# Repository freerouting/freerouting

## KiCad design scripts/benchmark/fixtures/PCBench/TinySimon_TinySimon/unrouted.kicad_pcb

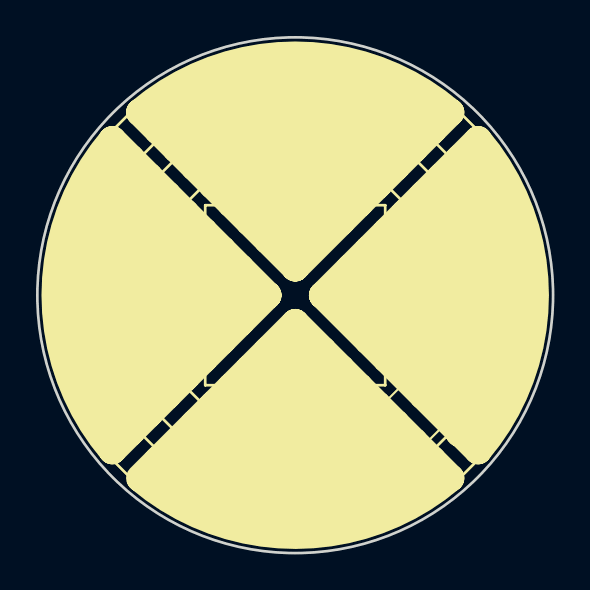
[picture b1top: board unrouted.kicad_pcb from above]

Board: 2 copper layers, 28.7 x 28.7 mm, 20 parts (0 on the bottom side), 10 nets, no tracks yet.

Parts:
B1: CR2032; BAT-HLD-001
D1: APT3216LSECK/J3-PRV; LED_1206
D2: APT3216LSYCK/J3-PRV; LED_1206
D3: APT3216LZGCK; LED_1206
D4: APT3216LVBC/D; LED_1206
P1: PIC ICSP; Pads_1x5_Pitch1.27mm
R1, R2, R3, R4: 1M; R_1206
R6, R7, R8, R9: 1K; R_1206
SW1, SW2, SW3, SW4: FSMSM; SW_SPST_FSMSM
U1: PIC10F200T; SOT-23-6
Y1: PKMCS0909E4000-R1; Murata_Piezo_SMD_9x9mm

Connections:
+BATT: B1.1, P1.2, R1.1, R2.1, R3.1, R4.1, U1.5
GND: B1.2, P1.3, SW1.2, SW2.2, SW3.2, SW4.2, U1.2
unnamed: D1.1, D2.2, R1.2, R7.1, R9.2, SW1.1
unnamed: D1.2, D2.1, D3.1, D4.2, R3.2, R6.1, SW3.1
unnamed: D3.2, D4.1, R4.2, R8.1, SW4.1, Y1.2
unnamed: P1.1, R2.2, SW2.1, U1.6
unnamed: P1.4, R6.2, U1.1
unnamed: P1.5, R7.2, U1.3
unnamed: R8.2, U1.4
unnamed: R9.1, Y1.1

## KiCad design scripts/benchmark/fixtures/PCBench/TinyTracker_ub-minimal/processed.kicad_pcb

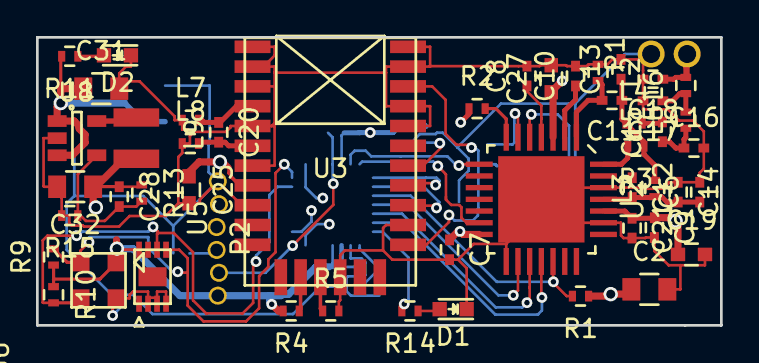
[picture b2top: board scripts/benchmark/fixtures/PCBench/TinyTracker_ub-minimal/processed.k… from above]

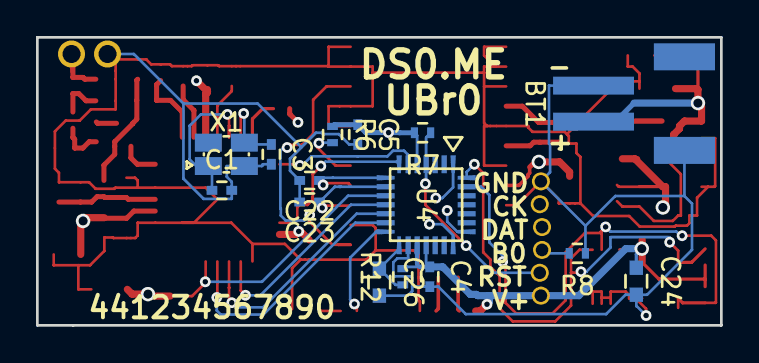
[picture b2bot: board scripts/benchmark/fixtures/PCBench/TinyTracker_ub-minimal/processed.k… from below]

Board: 4 copper layers, 38.0 x 16.0 mm, 65 parts (15 on the bottom side), 42 nets.

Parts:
BT1: LiPoly; S2B-PH-SM4-TB
C1, C3: 10p; C_0402
C2, C32: 10u; C_0805
C4, C5, C7, C8, C10: 100n; C_0402
C6: 10n; C_0402
C9, C12, C15: 47p; C_0402
C11: *2.2p; C_0402
C13: 6.8p; C_0402
C14: 100p; C_0402
C16: 15p; C_0402
C17: 12p; C_0402
C18: 4.7p; C_0402
C19: 2.2u; C_0603
C20: 18p; C_0402
C21, C22, C23: 22p; C_0402
C24, C25, C26, C27: 1u; C_0603
C28: 8.2p; C_0402
C31: 4.7u; C_0805
D1: RED; LED-0603
D2: GREEN; LED-0603
L2: *18nH; R_0402
L3: 47nH; R_0402
L4: 22n; R_0402
L5: 12n; R_0402
L6: 18n; R_0402
L7, L8: DNP; R_0402
L9: 74479787222; Neosid_Inductor_SM-NE29_SMD1008
P1: ANT; ANT_50ohm
P2: CONN_01X06; 6-1.27mm
R1, R2, R4, R5, R6, R9, R10: 10k; R_0402
R3: 0; R_0402
R7, R8, R12, R15: 100k; R_0402
R11: 2.2k; R_0402
R13: 300k; R_0402
R14: 220; R_0402
U2: SX1276; QFP_28_0.65
U3: M10478; M10748
U4: STM32F048GUx; UFQFPN28
U5: CAT24M01; UDFN8
U6: MS5637
U8: LM3671; SOT-23-5
X1: 32M; XTAL-2x2.5

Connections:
+1V8: C2.1, C4.1, C5.1, C7.1, C9.1, C19.1, C21.1, C24.1, C25.1, C27.1, C28.1, C32.1, L9.2, P2.1, R1.1, R2.1, R4.2, R6.1, R7.2, R9.1, R10.1, R12.2, R13.1, U2.3, U2.14, U2.24, U3.8, U4.5, U4.17, U4.18, U5.8, U6.1
+BATT: BT1.1, C31.1, R11.2, U8.1, U8.3
/LORA TX/ANT: C18.1, L6.2, P1.2
/LORA TX/DIO0: U2.8, U4.6
/LORA TX/DIO5: U2.13, U4.7
/LORA TX/MISO: U2.17, U4.12
/LORA TX/MOSI: U2.18, U4.13
/LORA TX/SCK: U2.16, U4.11
/MCU/GPS_RX: C23.1, U3.20, U4.9
/MCU/GPS_TX: C22.1, U3.21, U4.8
/MCU/I2C_SCL: R10.2, U4.27, U5.6, U6.3
/MCU/I2C_SDA: R9.2, U4.28, U5.5, U6.2
/MCU/LORA_~CS: R1.2, U2.19, U4.10
GND: BT1.2, C1.2, C2.2, C3.2, C4.2, C5.2, C6.2, C7.2, C8.2, C9.2, C10.2, C12.1, C13.2, C14.1, C16.2, C17.2, C18.2, C19.2, C21.2, C22.2, C23.2, C24.2, C25.2, C26.2, C27.2, C31.2, C32.2, D1.1, D2.1, L2.1, L7.1, L8.1, P1.3, P2.6, R5.2, R8.1, R15.2, U2.15, U2.23, U2.26, U2.29, U3.1, U3.2, U3.3, U3.5, U3.7, U3.9, U3.15, U3.19, U3.24, U3.25, U3.27, U3.28, U4.16, U5.2, U5.3, U5.4, U6.4, U8.2, X1.3
unnamed: C1.1, U2.5, X1.1
unnamed: C3.1, U2.6, X1.2
unnamed: C8.1, U2.4
unnamed: C10.1, U2.2
unnamed: C11.1, C13.1, L3.2, L4.1, R3.1
unnamed: C11.2, L2.2, U2.1
unnamed: C6.1, C12.2, C14.2, L3.1, U2.25
unnamed: C15.1, C16.1, L5.1
unnamed: C15.2, L4.2
unnamed: C17.1, L5.2, L6.1
unnamed: C20.1, L7.2, U3.4
unnamed: C20.2, L8.2, U3.6
unnamed: C26.1, R12.1, U4.15
unnamed: C28.2, R13.2, R15.1, U8.4
unnamed: D1.2, R14.1
unnamed: D2.2, R11.1
unnamed: L9.1, U8.5
unnamed: P2.2, R7.1, U4.4
unnamed: P2.3, R8.2, U4.1
unnamed: P2.4, U4.21
unnamed: P2.5, U4.22
unnamed: R2.2, U2.7
unnamed: R3.2, U2.28
unnamed: R4.1, U3.13
unnamed: R5.1, U3.14
unnamed: R6.2, U3.22
unnamed: R14.2, U4.14
unnamed: U3.18, U3.26

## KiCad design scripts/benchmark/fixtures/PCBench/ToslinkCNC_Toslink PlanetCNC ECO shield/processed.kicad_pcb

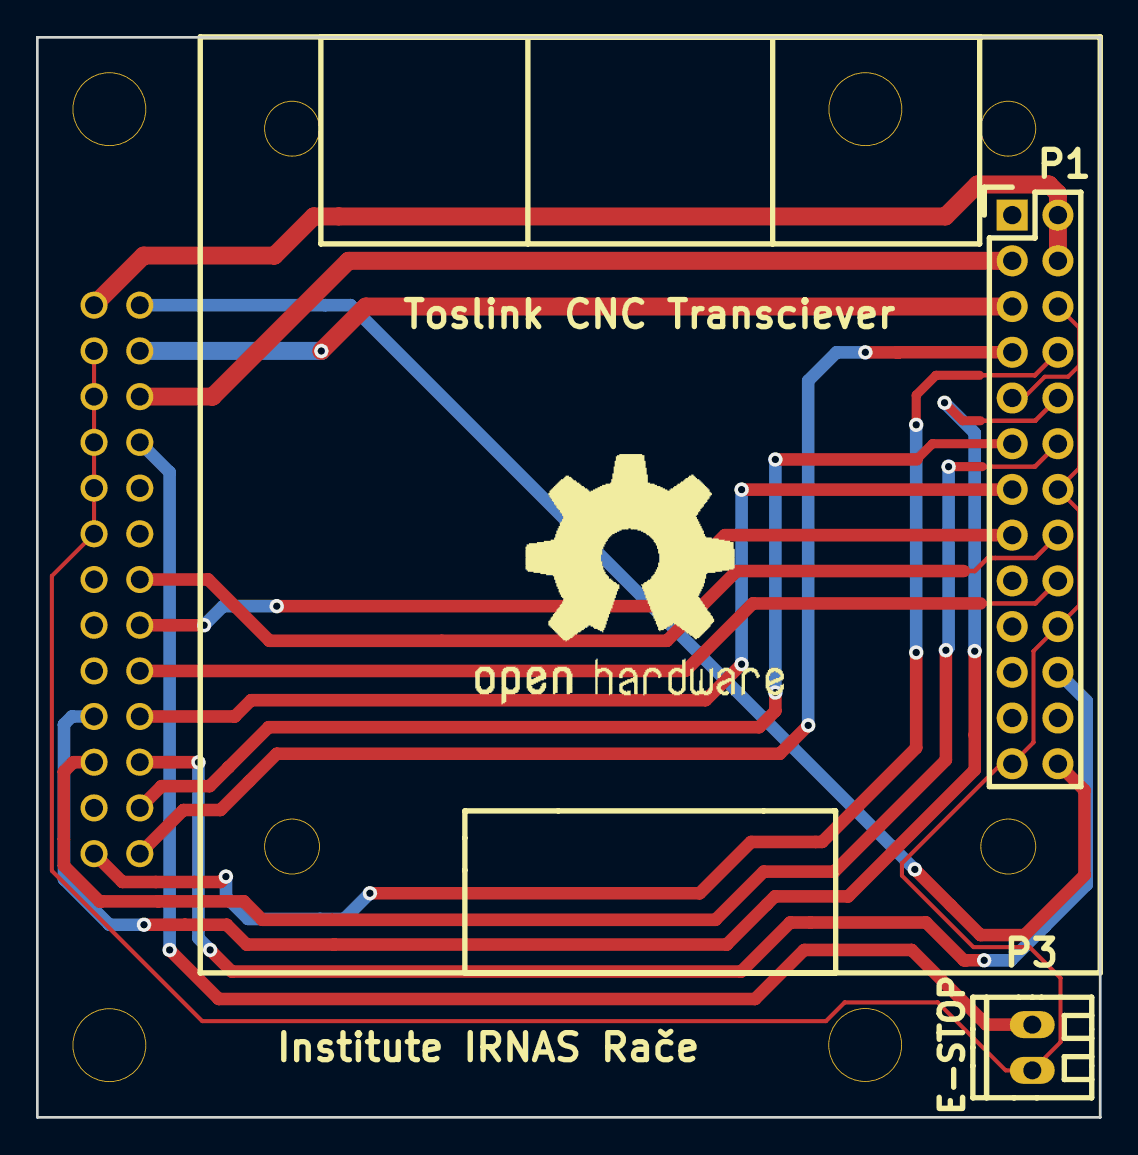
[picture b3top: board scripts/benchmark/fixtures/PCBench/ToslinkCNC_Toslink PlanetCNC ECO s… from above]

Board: 2 copper layers, 59.0 x 60.0 mm, 3 parts (0 on the bottom side), 16 nets.

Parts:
P1: Toslink CNC Transciever; toslink_pcb
P2: Planet CNC ECO PCB; PlanetCNC_ECO_PCB
P3: term_block; terminal_block_2_5mm

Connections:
+5V: P1.2, P1.4, P2.26
DIR_X: P1.22, P2.3
DIR_Y: P1.18, P2.5
DIR_Z: P1.16, P2.7
E-STOP: P2.10, P3.2
ENABLE: P1.7, P2.1
GND: P1.6, P1.9, P1.14, P1.20, P1.25, P2.21, P2.22, P2.23, P2.24, P2.25, P3.1
LIMIT_X: P1.3, P2.11
LIMIT_Y: P1.5, P2.12
LIMIT_Z: P1.26, P2.13
STEP_X: P1.11, P2.2
STEP_Y: P1.13, P2.4
STEP_Z: P1.15, P2.6
TRIGGER1: P1.12, P2.16
TRIGGER2: P1.10, P2.17
TRIGGER3: P1.8, P2.14

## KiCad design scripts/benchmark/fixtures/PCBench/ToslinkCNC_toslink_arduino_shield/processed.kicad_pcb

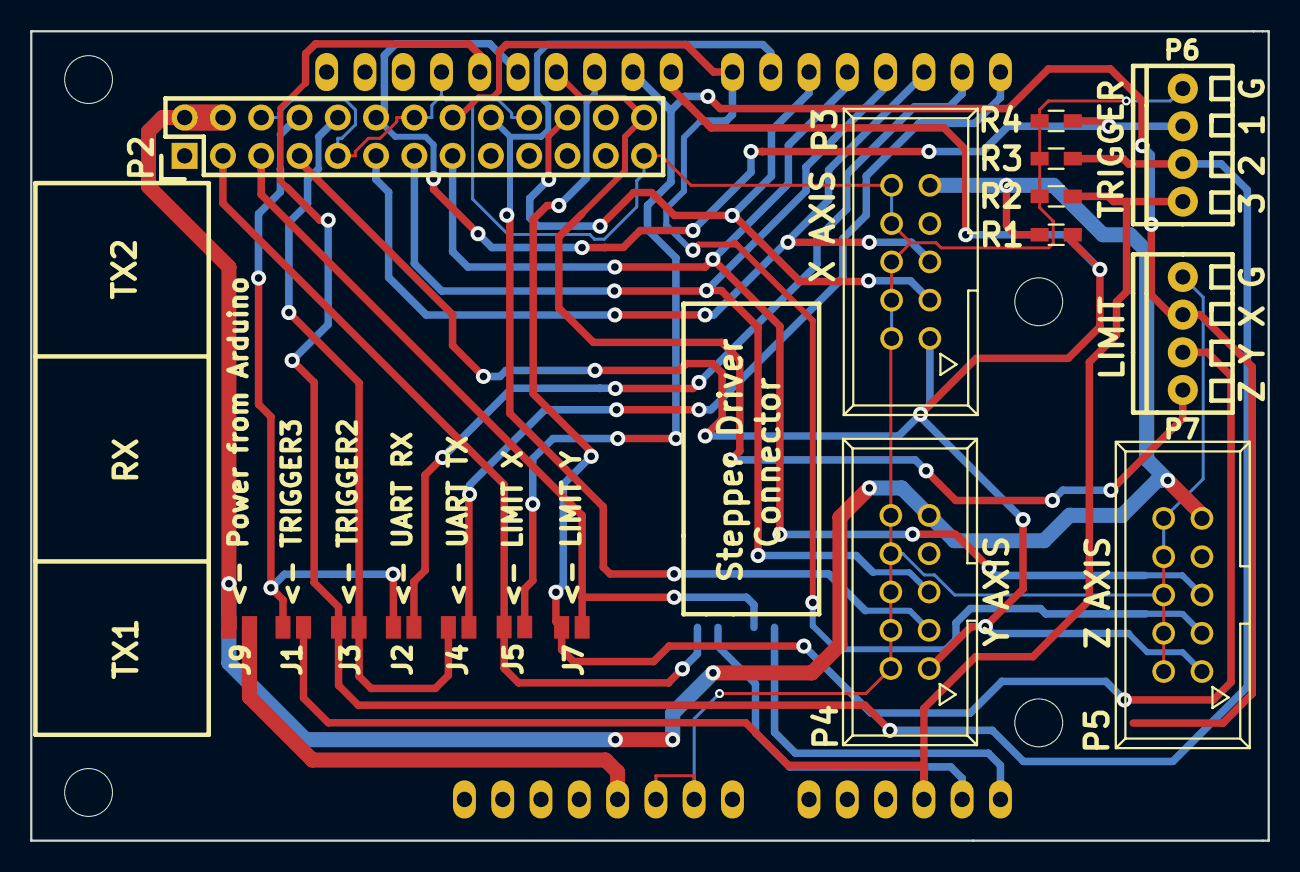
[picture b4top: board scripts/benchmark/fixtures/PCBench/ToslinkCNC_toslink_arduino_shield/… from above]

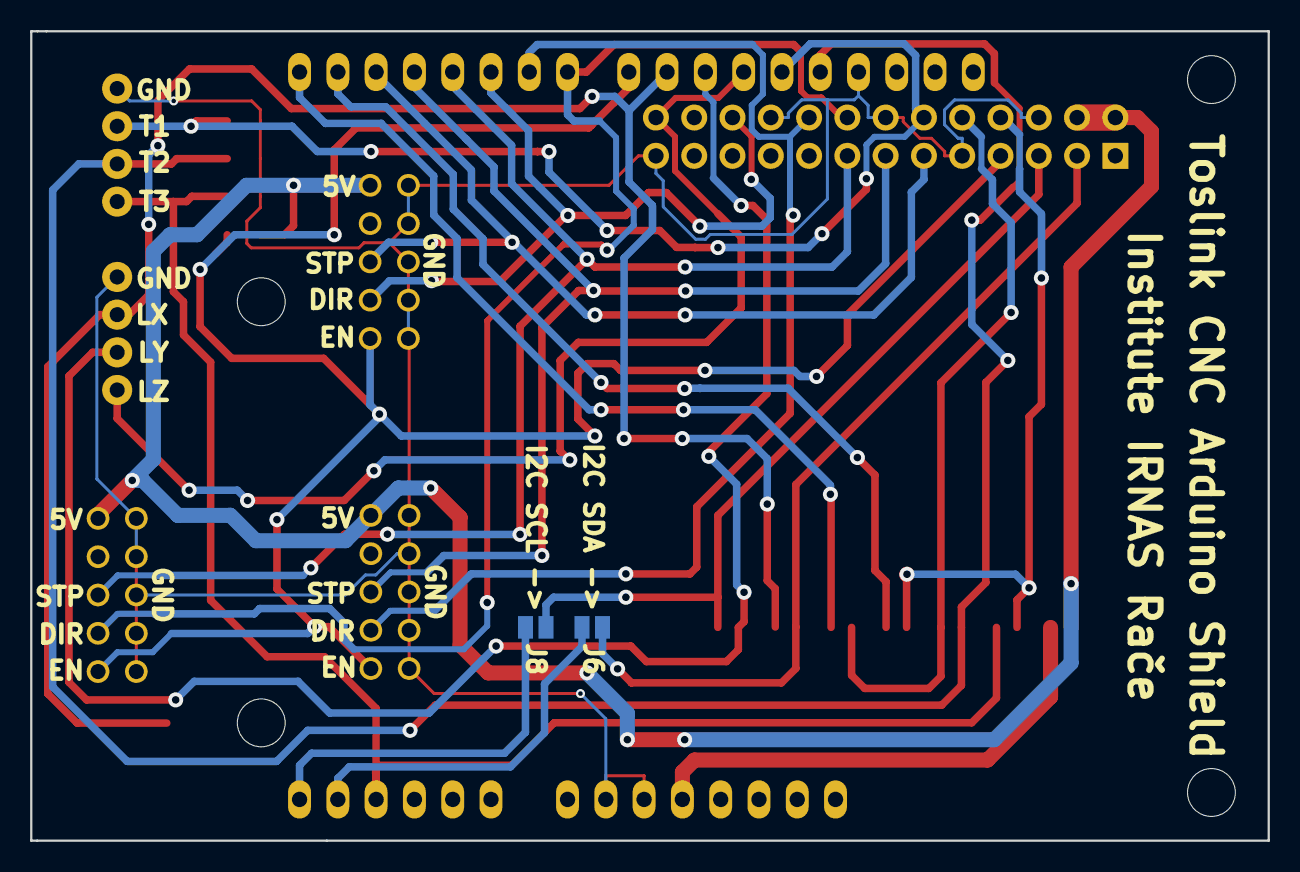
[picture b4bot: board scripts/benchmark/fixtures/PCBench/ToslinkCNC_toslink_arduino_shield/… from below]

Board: 2 copper layers, 82.1 x 53.7 mm, 20 parts (2 on the bottom side), 24 nets.

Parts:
J1, J2, J3, J4, J5, J6, J7, J8, J9: solder_bridge
P1: Arduino UNO; ARDUINO_SHIELD
P2: Toslink CNC Transciever; toslink_pcb
P3, P4, P5: PoStep25-32_connector; VASCH5x2
P6, P7: CONN_01X04; terminal_block_2_5mm_4pole
R1, R2, R3, R4: 10K; R_0603_HandSoldering

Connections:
+5V: J9.2, P2.2, P2.4, P3.9, P4.9, P5.9, R1.1
DIR_X: P1.5, P2.22, P3.3
DIR_Y: P1.6, P2.18, P4.3
DIR_Z: P1.7, P2.16, P5.3
ENABLE: P1.8, P2.7, P3.1, P4.1, P5.1, R1.2
GND: P1.GND1, P1.GND2, P1.GND3, P2.6, P2.9, P2.14, P2.20, P2.25, P3.2, P3.4, P3.6, P3.8, P3.10, P4.2, P4.4, P4.6, P4.8, P4.10, P5.2, P5.4, P5.6, P5.8, P5.10, P6.4, P7.4, R2.1, R3.1, R4.1
I2C_SCL: J8.2, P1.AD5
I2C_SDA: J6.2, P1.AD4
LIMIT_X: J5.2, P1.9, P7.3
LIMIT_X/I2C_SDA: J5.1, J6.1, P2.3
LIMIT_Y: J7.2, P1.10, P7.2
LIMIT_Y/I2C_SCL: J7.1, J8.1, P2.5
LIMIT_Z: P1.11, P2.26, P7.1
POWER: J9.1, P1.5V
STEP_X: P1.2, P2.11, P3.5
STEP_Y: P1.3, P2.13, P4.5
STEP_Z: P1.4, P2.15, P5.5
TRIGGER1: P1.12, P2.12, P6.3, R4.2
TRIGGER2: J3.2, P1.13, P6.2, R3.2
TRIGGER2/UART_TX: J3.1, J4.1, P2.10
TRIGGER3: J1.2, P1.AD3, P6.1, R2.2
TRIGGER3/UART_RX: J1.1, J2.1, P2.8
UART_RX: J2.2, P1.1
UART_TX: J4.2, P1.0
